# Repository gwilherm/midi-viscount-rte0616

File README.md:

# MIDI Viscount RTE0616

MIDIfied Viscount 270 Pedalboard "RTE0616"

## Compile and flash

Compile using arduino-cli

```
cd firmware/firmware
make
make upload
```

## Unit tests

```
cd firmware
mkdir build; cd build
cmake ..
make
make test
```

## Configuration App

### Install dependencies

```
cd rte0616-config-app
npm install
```

### Web

```
cd rte0616-config-app
npm run build:web
npm run start:web
```

### Desktop (electron)

```
cd rte0616-config-app
npm run build:desktop
npm run start:desktop
```

# Schematics

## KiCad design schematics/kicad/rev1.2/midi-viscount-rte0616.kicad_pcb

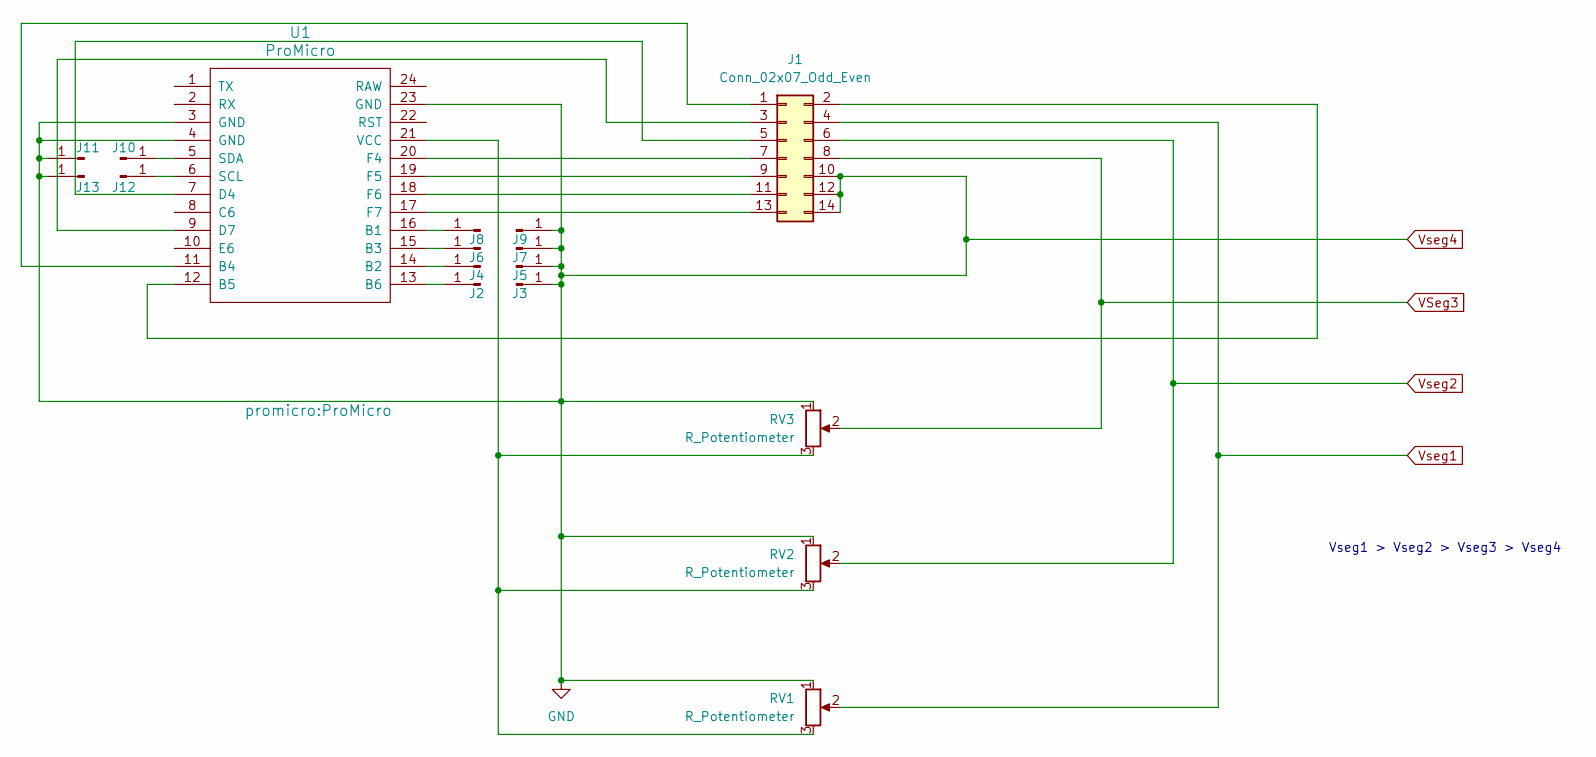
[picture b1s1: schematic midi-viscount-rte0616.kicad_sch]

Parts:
J1: Conn_02x07_Odd_Even; IDC-Header_2x07_P2.54mm_Vertical
J2, J3, J4, J5, J6, J7, J8, J9, J10, J11, J12, J13: Conn_01x01_Pin; PinHeader_1x01_P2.54mm_Vertical
RV1, RV2, RV3: R_Potentiometer; Potentiometer_Bourns_3296W_Vertical
U1: ProMicro

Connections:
unnamed: J1.1, U1.11 (B4)
unnamed: J1.2, U1.12 (B5)
unnamed: J1.3, U1.9 (D7)
unnamed: J1.5, U1.7 (D4)
unnamed: J1.7, U1.20 (F4)
unnamed: J1.9, U1.19 (F5)
unnamed: J1.11, U1.18 (F6)
unnamed: J1.13, U1.17 (F7)
unnamed: J2.1, U1.13 (B6)
unnamed: J4.1, U1.14 (B2)
unnamed: J6.1, U1.15 (B3)
unnamed: J8.1, U1.16 (B1)
unnamed: J10.1, U1.5 (SDA)
unnamed: J12.1, U1.6 (SCL)
unnamed: RV1.3, RV2.3, RV3.3, U1.21 (VCC)
VSeg3: J1.8, RV3.2
Vseg1: J1.4, RV1.2
Vseg2: J1.6, RV2.2
Vseg4: J1.10, J1.12, J1.14, J3.1, J5.1, J7.1, J9.1, J11.1, J13.1, RV1.1, RV2.1, RV3.1, U1.3 (GND), U1.4 (GND), U1.23 (GND)

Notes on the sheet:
Vseg1 > Vseg2 > Vseg3 > Vseg4

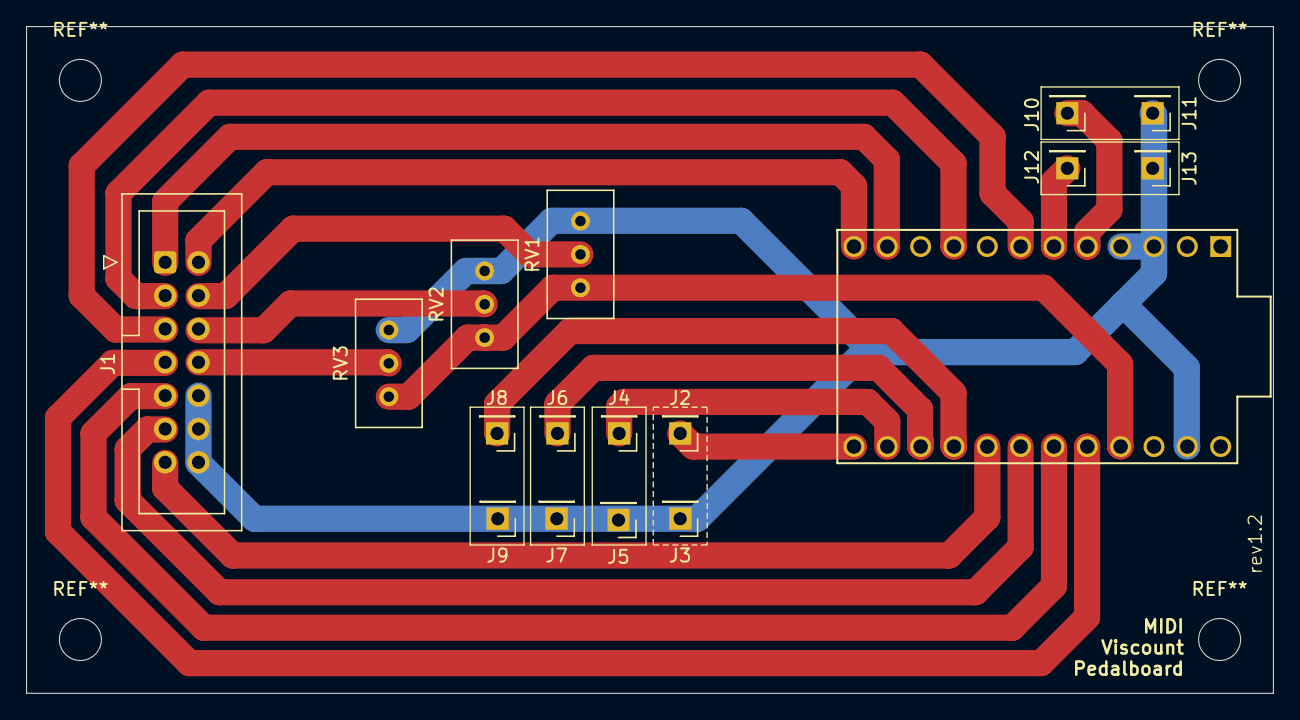
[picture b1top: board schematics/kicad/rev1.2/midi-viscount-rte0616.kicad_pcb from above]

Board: 2 copper layers, 95.0 x 50.8 mm, 17 parts (0 on the bottom side), 19 nets.

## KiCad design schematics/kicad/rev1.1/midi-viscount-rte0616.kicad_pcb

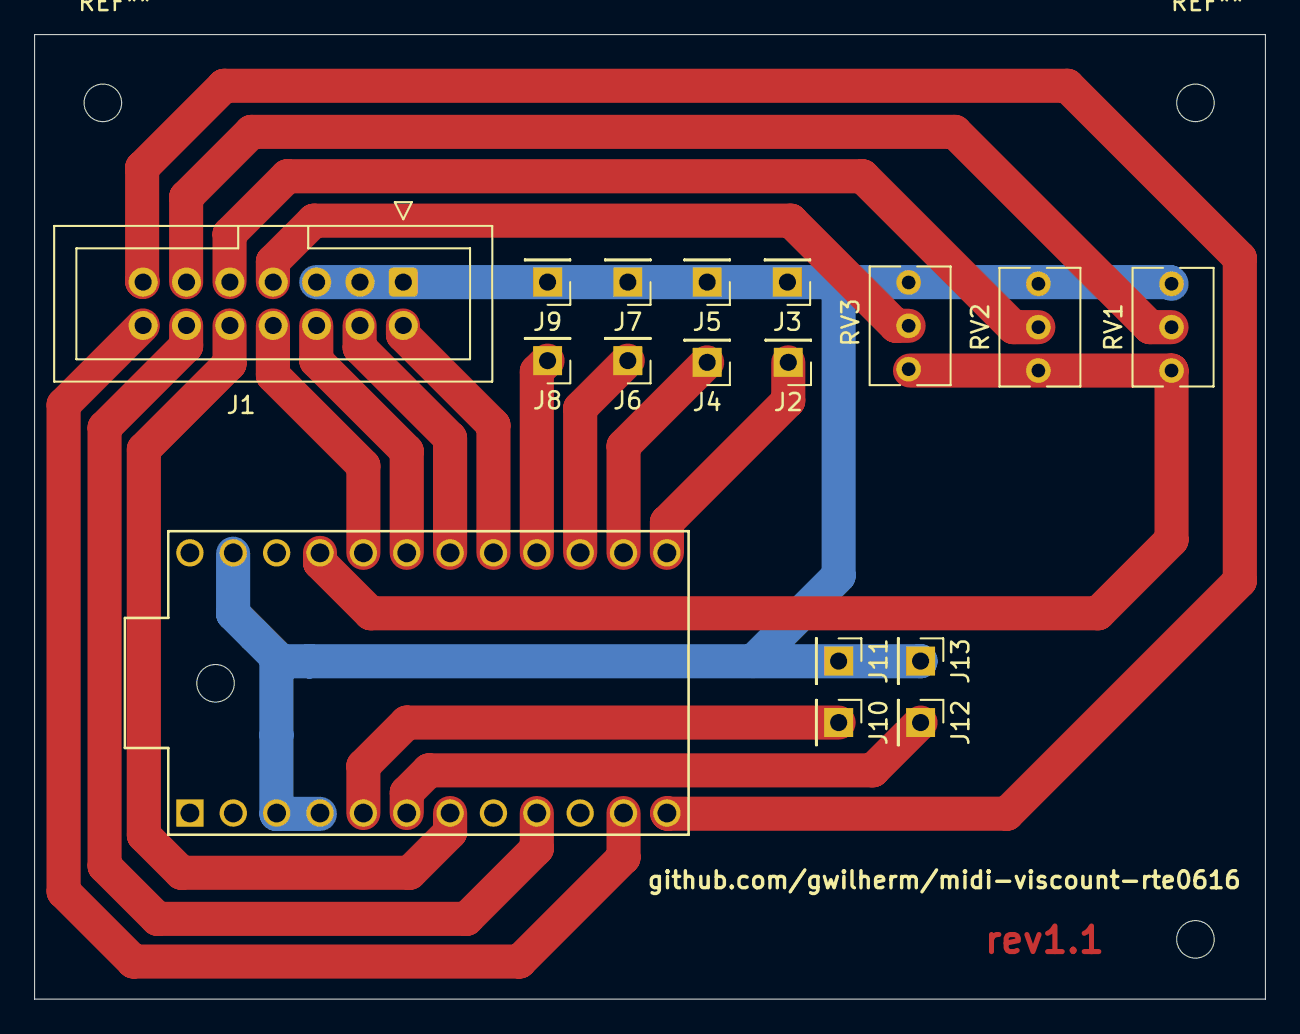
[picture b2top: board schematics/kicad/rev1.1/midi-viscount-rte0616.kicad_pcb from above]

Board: 2 copper layers, 72.1 x 56.5 mm, 17 parts (0 on the bottom side), 19 nets.

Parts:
J1: Conn_02x07_Odd_Even; IDC-Header_2x07_P2.54mm_Vertical
J2, J3, J4, J5, J6, J7, J8, J9, J10, J11, J12, J13: Conn_01x01_Pin; PinHeader_1x01_P2.54mm_Vertical
RV1, RV2, RV3: R_Potentiometer; Potentiometer_Bourns_3266Y_Vertical
U1: ProMicro

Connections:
unnamed: J1.2, U1.17 (F7)
unnamed: J1.4, U1.18 (F6)
unnamed: J1.6, U1.19 (F5)
unnamed: J1.8, U1.20 (F4)
unnamed: J1.10, U1.7 (D4)
unnamed: J1.12, U1.9 (D7)
unnamed: J1.13, U1.12 (B5)
unnamed: J1.14, U1.11 (B4)
unnamed: J2.1, U1.13 (B6)
unnamed: J4.1, U1.14 (B2)
unnamed: J6.1, U1.15 (B3)
unnamed: J8.1, U1.16 (B1)
unnamed: J10.1, U1.5 (SDA)
unnamed: J12.1, U1.6 (SCL)
unnamed: RV1.3, RV2.3, RV3.3, U1.21 (VCC)
VSeg3: J1.7, RV3.2
Vseg1: J1.11, RV1.2
Vseg2: J1.9, RV2.2
Vseg4: J1.1, J1.3, J1.5, J3.1, J5.1, J7.1, J9.1, J11.1, J13.1, RV1.1, RV2.1, RV3.1, U1.3 (GND), U1.4 (GND), U1.23 (GND)

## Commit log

2024-04-27 Add SysEx identification
2024-04-27 Add measure mode
2024-04-28 Compile using arduino-cli
2024-04-28 Calibration
2024-04-29 Fix segments indexes
2024-05-06 Firmware version + handle get/set configuration
2024-05-07 Add prefix to measures sysex message
2024-05-07 Attempt to make a web app with angular
2024-05-07 Add electron client
2024-05-07 ng add @angular/material
2024-05-07 Add tab navigation
2024-05-07 MidiService
2024-05-07 Receive ident response
2024-05-07 Get measures
2024-05-07 Configuration component
2024-05-07 Fix parsing ident response
2024-05-07 Identify
2024-05-07 Route guard already satisfying the redirection
2024-05-07 Fix two way binding
2024-05-07 Add device component
2024-05-07 Add identify and continue button
2024-05-07 Get calibration
2024-05-07 Reset configuration form
2024-05-07 Fix sysex support
2024-05-07 UI improvments
2024-05-07 Add igniteui linear gauges
2024-05-08 Limit CPU usage using throttleTime
2024-05-08 Improve ui
2024-05-08 Send calibration
2024-05-09 Layout: I have no idea what I'm doing
2024-05-09 Use arrays for vSeg
2024-05-09 More constants
2024-05-10 Basic sw debounce
2024-05-11 WIP improve debounce
2024-05-12 WIP refactoring
2024-05-18 Refactoring declare as static member instead of global variable
2024-05-18 refactoring: HardwareInterface
2024-05-19 Fix warnings
2024-05-19 HardwareInterface.setup unit test
2024-05-19 simple HardwareInterface.loop unit test
2024-05-19 more HardwareInterface.loop unit tests
2024-05-19 Use WillRepeatedly instead of WillByDefault
2024-05-19 Add SerialPrinter for tests
2024-05-19 HardwareInterface.loop unit tests for release
2024-05-19 Realistic pinMode mock
2024-05-20 Make mockable USB MIDI Interface
2024-05-20 MIDISysexInterface handleGetCalibration and handleSetCalibration unit tests
2024-05-20 MIDISysexInterface handleGetConfiguration and handleSetConfiguration unit tests
2024-05-20 Bugfix
2024-05-20 MIDISysexInterface handleMeasuresRequest and sendMeasures unit tests
2024-05-20 Add MIDINotesService
2024-05-21 Mockable HardwareInterface and new MIDINotesService unit tests
2024-05-21 Use potentiometers instead of resistors
2024-05-21 Config App: decode firmware version
2024-05-21 Config App: Resize window and hide devtools
2024-05-21 Config App: Workaround for reload menu
2024-05-23 Add pin headers for pedals
2024-05-23 Add footswitches and expression pedal inputs
2024-05-23 Fix footswitch reading
2024-05-23 Update schematics
2024-05-24 I prefix for interfaces
2024-05-24 Implement MIDICCService
2024-05-24 Add unit tests for pedals
2024-05-26 Simplify sysex commands
2024-05-26 Bump version
2024-05-28 npx electron-forge import
2024-05-28 remove FW_DEBUG flag
2024-05-28 Bump config app version
2024-05-29 Update gitignore
2024-05-29 Add MemoryService and tests
2024-05-31 Add device info marker to memory
2024-06-01 Use a struct for device info
2024-06-02 Overcomplicated
2024-06-02 Use offsetof
2024-06-02 Use full memory struct in restore
2024-06-02 Clean
2024-06-02 Fix MemoryService instanciation
2024-06-02 Reduce complexity
2024-06-02 Add SysEx commands for memory management
2024-06-02 Config App: store config and calibration
2024-06-02 Fix SysexService instanciation
2024-06-15 Schematics rev1.1
2024-06-15 Schematics rev1.2
2024-06-23 Quick fix for the inverted IDC header...
2024-06-23 Update docs
    Update docs
2024-07-15 Remove useless loop
2024-07-15 WIP Polyphonic mode
2024-07-15 Save keyboard mode to memory
2024-07-15 Change order of stored information
2024-07-17 Add keyboard mode to midi config sysex command
2024-07-20 manage keyboard modes in a testable way
2024-07-20 Use constants
2024-07-21 factory reset on major version update
2024-07-21 Rename Pedal to Extra Pedal
